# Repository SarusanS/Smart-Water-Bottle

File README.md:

# Project Highlight | Product Design – Smart Water Bottle

This project presents a **standalone Smart Water Bottle** developed as part of a **Product Design course**, focused on accurate, motion-aware water consumption monitoring under real-world usage conditions such as **movement, refilling, and power interruptions**.

The system is **fully embedded** and operates independently **without requiring a mobile application**, prioritizing **reliability, usability, and data integrity**.

---

## System Functionality

Water consumption is monitored by tracking changes in liquid level using a **VL53L0X Time-of-Flight (ToF) distance sensor**. Instead of relying on the absolute bottle capacity, the system calculates consumed volume based on **successive stable distance measurements**, allowing cumulative tracking across multiple refill cycles.

Even if the physical bottle capacity is limited (e.g., **1 litre**), users can configure daily intake goals of **5 L, 10 L, or 15 L**. Each refill is automatically detected as an **increase in water level**, while subsequent decreases are accumulated to compute **total consumption over time**.  
This approach enables **continuous and scalable intake monitoring**, independent of bottle size.

---

## Motion-Aware Validation

To ensure measurement accuracy, the system integrates a **BMI270 Inertial Measurement Unit (IMU)** combined with a **Madgwick sensor fusion filter**.

- Distance measurements are accepted only when the bottle is **upright and stable**
- **Tilt, motion, shaking, lifting, and refilling events** are detected and filtered out
- A **stability verification delay** ensures readings are taken only after motion has fully stopped

This motion-aware logic prevents **false volume calculations** and significantly improves measurement reliability during **daily use**.

---

## Floating Reflective Marker for Accurate Measurement

To overcome the challenges of measuring water level in transparent containers, a **floating reflective marker** is used:

- A small **floating rubber disc** is placed directly on the water surface
- The ToF sensor reflects off the **rubber surface instead of the water itself**
- This avoids errors caused by **ripples, bubbles, refraction, or transparent bottle walls**

As the marker naturally follows the water surface, the system achieves **consistent and repeatable distance measurements**, which are converted into volume through **firmware-level calculations**.

---

## Operating Modes

### Mode 1 – Goal-Based Tracking
- User-configurable **daily intake goal**
- Tracks **daily water consumption**
- Automatically **resets every 24 hours**
- Stores **previous day’s consumption** for reference

### Mode 2 – Continuous Tracking
- No predefined intake goal
- Tracks **total consumption continuously**
- **Manual reset** via touch-based confirmation
- Suitable for **long-term or unrestricted monitoring**

---

## User Interface and Interaction

- Touch-based input supports **display wake-up, goal setting, mode switching, and reset confirmation**
- **OLED display** presents real-time information including:
  - Water consumption
  - Daily goal status
  - Operating mode
  - Battery voltage
  - Time and date
- **Automatic display sleep** minimizes power consumption

---

## Touch Gesture Instructions

The system uses a **capacitive touch interface** to provide intuitive, button-less user interaction. Different tap patterns are interpreted by firmware to trigger specific actions.

| Gesture | Action |
|-------|--------|
| Single Tap | Increment value during goal or setting configuration |
| Double Tap | Wake the display or confirm a selection |
| Triple Tap | Switch between operating modes (Goal-Based / Continuous) |
| Long Inactivity | Automatically puts the display into sleep mode |

Touch input is **debounced and time-window validated** in firmware to prevent false triggers and ensure reliable gesture detection.

---

## Power and Battery Management

- Battery voltage is monitored in real time using the **ESP32 ADC**
- Status is displayed directly on the **OLED interface**
- Safe charging is handled externally via a **dedicated battery charging circuit**
- **Persistent storage** ensures data integrity across power cycles, supporting portable operation

---

## Hardware and PCB Design

- Custom **SMD-based PCB** designed for compact, reliable, and production-ready assembly
- Optimized component placement for:
  - Distance sensor
  - IMU
  - OLED display
  - Power management circuitry
- Designed to support **robust, portable, and scalable product deployment**

---

## Data Integrity and Reliability

- All critical parameters and usage data are stored in **non-volatile flash memory (ESP32 NVS)**
- Seamless recovery after **unexpected power loss**
- **Noise-filtered distance averaging and outlier rejection** improve measurement accuracy

---

## Technology Stack

- **Microcontroller:** ESP32  
- **Sensors:** VL53L0X ToF Sensor, BMI270 IMU  
- **Sensor Fusion:** Madgwick Filter  
- **Display:** SSD1306 OLED  
- **Input:** Touch Interface  
- **Storage:** ESP32 Non-Volatile Storage (NVS)  
- **Hardware:** Custom SMD PCB Design  

---

## Learning Outcomes

This project significantly strengthened my skills in:

- Embedded firmware development  
- Sensor fusion and motion-aware measurement  
- Robust signal processing for real-world conditions  
- Power-aware system design  
- SMD PCB design and hardware integration  
- User-centric embedded product development

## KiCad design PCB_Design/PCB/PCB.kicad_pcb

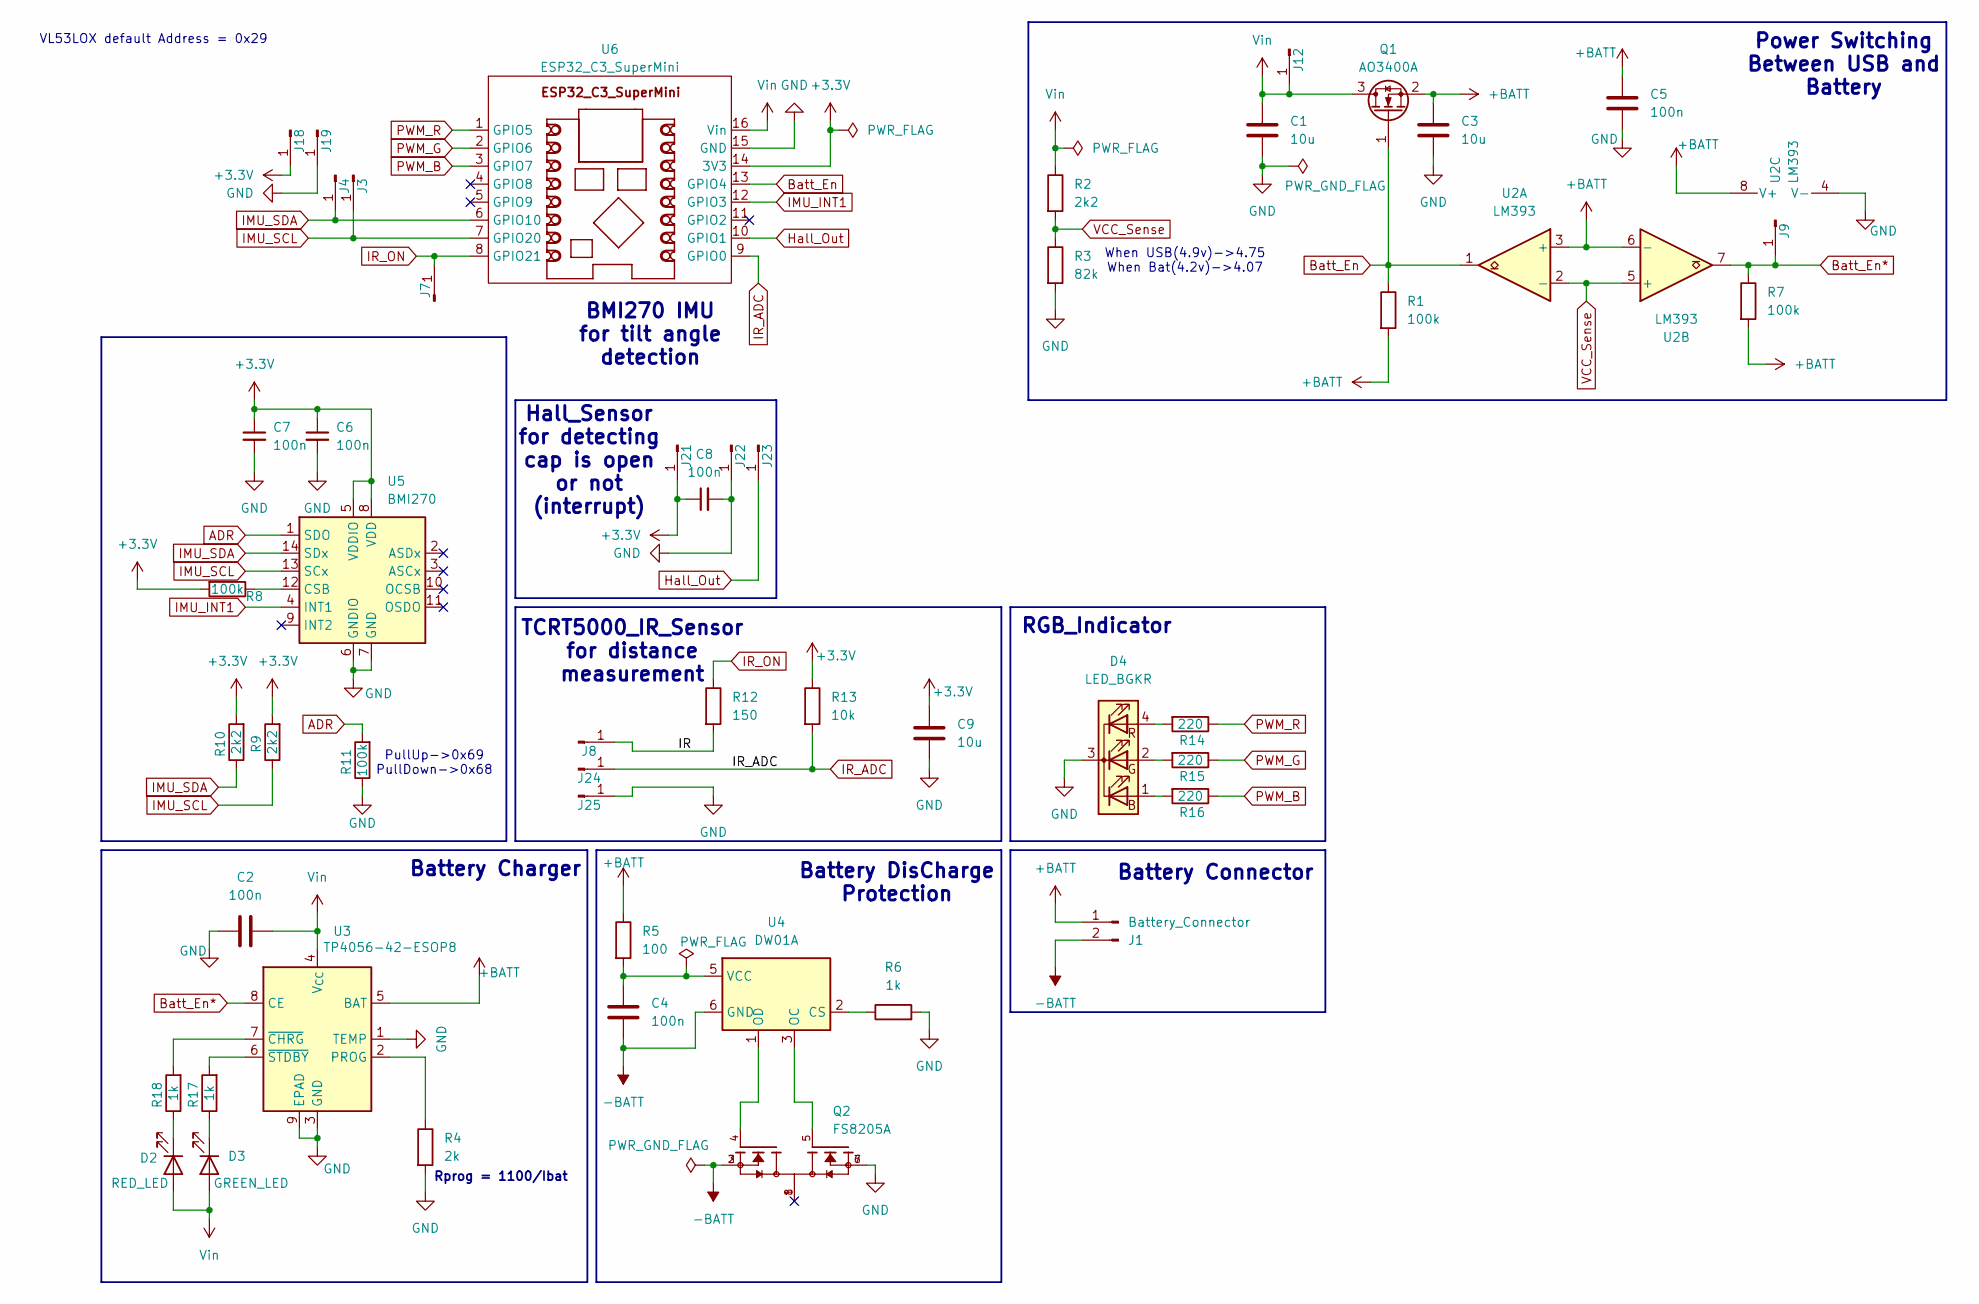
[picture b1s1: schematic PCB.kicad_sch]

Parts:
C1, C3, C9: 10u; C_0603_1608Metric
C2, C4, C5, C6, C7, C8: 100n; C_0603_1608Metric
D2: RED_LED; LED_0603_1608Metric
D3: GREEN_LED; LED_0805_2012Metric
D4: LED_BGKR; LED_D5.0mm-4_RGB_Wide_Pins_Bend_Horizontally
J1: Battery_Connector; TestPoint_2Pads_Pitch5.08mm_Drill1.3mm
J3, J4, J19, J22, J23, J24, J25: Conn_01x01_Pin; TestPoint_Pad_D1.5mm
J7: Conn_01x01_Pin; TestPoint_Pad_1.0x1.0mm
J8, J18, J21: Conn_01x01_Pin; TestPoint_Pad_1.5x1.5mm
J9, J12: Conn_01x01_Pin; TestPoint_Pad_D1.0mm
Q1: AO3400A; SOT-23
Q2: FS8205A; PARTREV 1.7
R1, R7, R8, R11: 100k; R_0402_1005Metric
R2: 2k2; R_0603_1608Metric
R3: 82k; R_0603_1608Metric
R4: 2k; R_0402_1005Metric
R5: 100; R_0402_1005Metric
R6: 1k; R_0402_1005Metric
R9, R10: 2k2; R_0402_1005Metric
R12: 150; R_0603_1608Metric
R13: 10k; R_0603_1608Metric
R14, R15, R16: 220; R_0603_1608Metric
R17, R18: 1k; R_0603_1608Metric
U2: LM393; SOIC-8_3.9x4.9mm_P1.27mm
U3: TP4056-42-ESOP8; SOIC-8-1EP_3.9x4.9mm_P1.27mm_EP2.41x3.3mm
U4: DW01A; SOT-23-6
U5: BMI270; Bosch_LGA-14_3x2.5mm_P0.5mm
U6: ESP32_C3_SuperMini

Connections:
+3.3V: C6.1, C7.1, C8.1, C9.1, J18.1, J21.1, R8.2, R9.2, R10.2, R13.1, U5.5 (VDDIO), U5.8 (VDD), U6.14 (3V3)
+BATT: C3.1, C5.1, J1.1, Q1.2 (S), R1.2, R5.1, R7.2, U2.3 (+), U2.6 (-), U2.8 (V+), U3.5 (BAT)
-BATT: C4.1, J1.2, Q2.2, Q2.3, U4.6 (GND)
/IR: J8.1, R12.2
ADR: R11.2, U5.1 (SDO)
Batt_En: Q1.1 (G), R1.1, U2.1, U6.13 (GPIO4)
Batt_En*: J9.1, R7.1, U2.7, U3.8 (CE)
GND: C1.2, C2.1, C3.2, C5.2, C6.2, C7.2, C8.2, C9.2, D4.3 (K), J19.1, J22.1, J25.1, Q2.6, Q2.7, R3.2, R4.2, R6.2, R11.1, U2.4 (V-), U3.1 (TEMP), U3.3 (GND), U3.9 (EPAD), U5.6 (GNDIO), U5.7 (GND), U6.15 (GND)
Hall_Out: J23.1, U6.10 (GPIO1)
IMU_INT1: U5.4 (INT1), U6.12 (GPIO3)
IMU_SCL: J3.1, R9.1, U5.13 (SCx), U6.7 (GPIO20)
IMU_SDA: J4.1, R10.1, U5.14 (SDx), U6.6 (GPIO10)
IR_ADC: J24.1, R13.2, U6.9 (GPIO0)
IR_ON: J7.1, R12.1, U6.8 (GPIO21)
unnamed: D2.1 (K), R18.1
unnamed: D3.1 (K), R17.1
unnamed: D4.1 (BA), R16.2
unnamed: D4.2 (GA), R15.2
unnamed: D4.4 (RA), R14.2
unnamed: R4.1, U3.2 (PROG)
unnamed: R18.2, U3.7 (~CHRG)
unnamed: R17.2, U3.6 (~STDBY)
unnamed: R6.1, U4.2 (CS)
unnamed: Q2.5, U4.3 (OC)
unnamed: Q2.4, U4.1 (OD)
unnamed: C4.2, R5.2, U4.5 (VCC)
unnamed: R8.1, U5.12 (CSB)
PWM_B: R16.1, U6.3 (GPIO7)
PWM_G: R15.1, U6.2 (GPIO6)
PWM_R: R14.1, U6.1 (GPIO5)
VCC_Sense: R2.2, R3.1, U2.2 (-), U2.5 (+)
Vin: C1.1, C2.2, D2.2 (A), D3.2 (A), J12.1, Q1.3 (D), R2.1, U3.4 (V_{CC}), U6.16 (Vin)

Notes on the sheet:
BMI270 IMU for tilt angle detection
PullUp->0x69 PullDown->0x68
Power Switching Between USB and Battery
Hall_Sensor for detecting cap is open or not (interrupt)
Battery Connector
When USB(4.9v)->4.75 When Bat(4.2v)->4.07
Battery DisCharge Protection
Rprog = 1100/Ibat
Battery Charger
VL53LOX default Address = 0x29
TCRT5000_IR_Sensor for distance measurement
RGB_Indicator

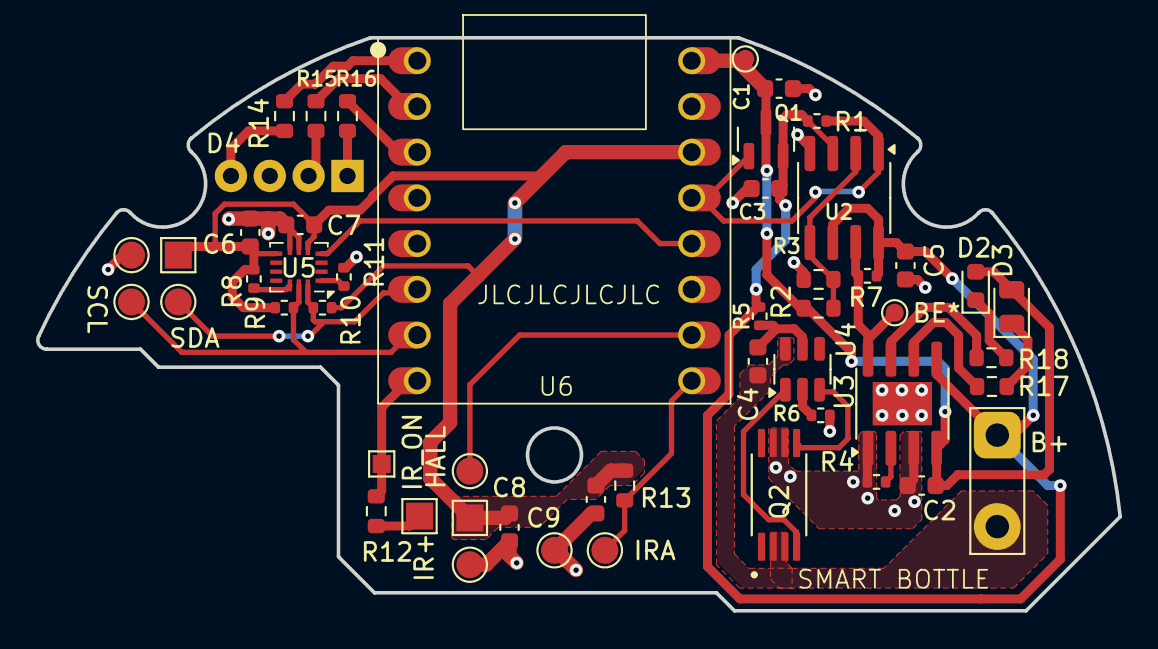
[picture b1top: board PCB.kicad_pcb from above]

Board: 2 copper layers, 60.1 x 31.8 mm, 51 parts (0 on the bottom side), 32 nets.

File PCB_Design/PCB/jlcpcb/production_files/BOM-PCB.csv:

Comment,Designator,Footprint,LCSC,Quantity
100,R5,R_0402_1005Metric,C25076,1
100k,"R1,R11,R7,R8",R_0402_1005Metric,C25741,4
100n,"C2,C4,C5,C6,C7,C8",C_0603_1608Metric,C14663,6
10k,R13,R_0603_1608Metric,C25804,1
10u,"C1,C3,C9",C_0603_1608Metric,C96446,3
150,R12,R_0603_1608Metric,C22808,1
1k,R6,R_0402_1005Metric,C11702,1
1k,"R17,R18",R_0603_1608Metric,C21190,2
220,"R14,R15,R16",R_0603_1608Metric,C22962,3
2k,R4,R_0402_1005Metric,C4109,1
2k2,"R10,R9",R_0402_1005Metric,C25879,2
2k2,R2,R_0603_1608Metric,C4190,1
82k,R3,R_0603_1608Metric,C23254,1
AO3400A,Q1,SOT-23,C20917,1
BMI270,U5,Bosch_LGA-14_3x2.5mm_P0.5mm,C2836813,1
DW01A,U4,SOT-23-6,C42380662,1
FS8205A,Q2,FS8205A,C2830320,1
GREEN_LED,D3,LED_0805_2012Metric,C5878902,1
LM393,U2,SOIC-8_3.9x4.9mm_P1.27mm,C7955,1
RED_LED,D2,LED_0603_1608Metric,C2286,1
TP4056-42-ESOP8,U3,SOIC-8-1EP_3.9x4.9mm_P1.27mm_EP2.41x3.3mm,C22470410,1

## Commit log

2026-01-30 All Necessary Files are uploaded
2026-01-30 Add project details for Smart Water Bottle
    Added detailed project overview and system functionality for the Smart Water Bottle, including motion-aware validation, user interface, power management, and technology stack.
